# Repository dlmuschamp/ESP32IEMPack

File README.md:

# ESP32 Wireless IEM Pack

A first-pass wireless in-ear monitor (IEM) system: one ESP32 transmitter pack and one ESP32 receiver pack. The RX path is `ESP-NOW → ESP32 → I2S → PCM5102 DAC → volume pot → MAX97220A headphone amp → 3.5 mm jack`.

This repo is a work in progress. The breadboard version plays audio. The KiCad project in `KiCad/RX_SKETCHES/` is that breadboard transferred onto hierarchical sheets — not a finished layout. There is **no display on this version**.

## What this version is (and is not)

| | This version | Not this version |
|---|---|---|
| Display | None | The old 1.54" TFT / Arduino UI idea |
| RX power | USB-C from a 10,000 mAh 5 V power bank → LM3940 3.3 V | TP4056 + 2000 mAh LiPo / 3xAA |
| TX power | The same kind of 10,000 mAh 5 V power bank as the RX | A different battery chemistry or a shared bank |
| Radio | ESP32-WROOM-32U + **`ANT1` 2.4 GHz U.FL pigtail** on `esp_rx` | On-module PCB antenna (that is the 32E / 32D) |
| Audio | I2S to a PCM5102, then a headphone amp | I2C (the DAC is I2S) |
| PCB | Footprint dump / ratsnest only | Routed board ready to order |

TX and RX each get their **own** identical 10,000 mAh bank. Do not power both packs from one bank if you want them to roam independently.

## Repo map

```
main/                  ESP-IDF C firmware
  rig_shared.h         Shared packet / state types (TX and RX)
  tx.c                 Transmitter (ESP-NOW + ADC pot + LED). Audio fill is still TODO.
  rx.c                 Receiver stub. Set IEM_NODE=RX when it has an app_main.
  square_wave_test.c   Bench I2S tone used to prove the DAC path
  sniffer.c            Monitor / debug helper
KiCad/RX_SKETCHES/     RX hierarchical schematic (WIP)
KiCad/TX_SKETCHES/     TX placeholder
KiCad/Custom_Part_Downloads/  SnapEDA symbols / footprints used by the RX project
```

Build a node with ESP-IDF after exporting the target:

```bash
IEM_NODE=TX idf.py build
# IEM_NODE=RX or IEM_NODE=MON once those mains are complete
```

`main/CMakeLists.txt` refuses to build if `IEM_NODE` is missing. That is intentional so you do not flash the wrong image.

## Hardware (RX 1.0.0 KiCad)

Hierarchical sheets, in signal order:

1. **`pwr_mgmt`** — USB-C (CC pulldowns), CP2102C UART bridge, LM3940 5 V → 3.3 V
2. **`esp_rx`** — ESP32-WROOM-32U + `ANT1` (U.FL pigtail / 2.4 GHz antenna)
3. **`dac`** — PCM5102
4. **`vol_ctrl`** — dual-gang log pot + 0% switch
5. **`amp`** — MAX97220A to the 3.5 mm jack

### Firmware I2S map (do not "improve" these GPIOs)

These match the working breadboard and `main/square_wave_test.c`:

| Hierarchical label | ESP32 GPIO | Firmware name |
|---|---|---|
| `BCK` | IO33 | `BCK_PIN` |
| `LRCLK` | IO32 | `LRCK_PIN` |
| `DIN` | IO25 | `DOUT_PIN` (ESP data **out** to the DAC data **in**) |

UART programming: `TXD` = TXD0/IO1, `RXD` = RXD0/IO3. Auto-program straps: `ESP_EN` = EN, `ESP_IO0` = IO0.

### Antenna (`ANT1` on `esp_rx`)

The **32U** module has a U.FL connector and **no PCB antenna**. `ANT1` is a BOM / documentation part: a **2.4 GHz, 50 Ω antenna on a U.FL / IPEX pigtail** that mates to the connector already on the module. It is not wired to a GPIO. It has no PCB footprint — you buy the pigtail, you do not etch an antenna.

If you would rather have an on-board antenna later, that is a different module (WROOM-32E / 32D), not a missing copper pour on the 32U.

### Analog (PCM5102 datasheet vs experiments)

The PCM5102 datasheet analog network for a ~10 kΩ load is already on the DAC sheet (`R16`/`R17` 470 Ω, `C20`/`C21` 2.2 nF):

`OUTL/OUTR → 470 Ω series → PRE_POT`, with **2.2 nF from that node to GND**.

The MAX97220A input impedance is also about **10 kΩ**, so that filter is the right starting point. The experimental 1 kΩ / 10 Ω pad on `vol_ctrl` is **DNP**, with a short across the 1 kΩ positions so an empty series part does not open the audio path.

MAX97220A voltage gain is **fixed +3.5 dB**. Input network resistors `R1–R6`, `R9`, `R10` are **DNP** on hand-built protos so you can try values. Populate them (start 10 kΩ) only if you order a fully assembled board. Use a MAX97220**D** if you want resistor-programmed gain.

### Hand assembly

Schematic footprint fields are **0805**. Use 0805 for every resistor and capacitor you will solder yourself, including 10 / 22 / 33 µF. 0603 is OK if you are already comfortable. Do not use 0402 or 0201. The `.kicad_pcb` still shows 0201 until you **Update PCB from Schematic**.

ICs stay their real packages (WROOM module, TSSOP-20, TQFN-16, SOT-223, WQFN-24).

## Current status

- [x] Breadboard RX path plays (ESP32 I2S → PCM5102 → amp → IEMs)
- [x] Repo + KiCad folder split (`RX_SKETCHES` / `TX_SKETCHES`)
- [x] RX hierarchical schematic transferred from the breadboard (WIP)
- [x] Hierarchical labels rewired; `ANT1` added on `esp_rx`
- [ ] Buy / fit the U.FL pigtail; confirm ESP-NOW range
- [ ] Finish `tx.c` audio packet fill / `rx.c` I2S consume
- [ ] Run ERC, then floorplan and route the RX PCB
- [ ] TX schematic (same 10,000 mAh USB-C bank idea)

No TFT / SPI display work on this revision.

## Common KiCad / first-board mistakes

This is a first KiCad project *and* a first C / ESP-IDF / multi-IC audio board. The list below is the stuff that already bit this schematic. Check it every time you move a part or add a hierarchical label.

### 1. Rotating a symbol does not remap pin numbers

Pin 3 is still `EN` after a 270° rotate. KiCad only rotates the **drawing** and the **sheet coordinates** of the pins around the symbol origin. Hierarchical labels and wires that stay put will attach to whichever pin rotated into that spot.

After any rotate: click each pin, read the name, then move the label onto **that** pin. Do not assume “left side is still EN.”

### 2. Hierarchical labels connect through wires, not vibes

A label sitting near a pin is not connected. ERC and the ratsnest follow **wires and pin ends**. After a rotate, a label can look “on” the chip and still sit on empty space or on the wrong pin (`ESP_IO0` on `EN`, `BCK` on `DEMP`, `SHDN_SIGNAL` on `C1N`).

Triple-check every hierarchical label against the **pin name**, not the side of the box.

### 3. Same-ish names are different pins

| You meant | Easy to hit instead | What happens |
|---|---|---|
| PCM5102 `BCK` / `DIN` / `LRCK` | `DEMP` / `XSMT` / `FMT` | DAC never gets PCM; clocks toggle config bits |
| MAX97220 `~{SHDN}` | `C1N` (charge-pump cap) | Volume switch does not mute; VSS pump breaks |
| ESP `TXD0` / `RXD0` | `SENSOR_VN` / empty space | USB-C UART programming dies |
| I2S | I2C | Wrong bus, wrong pins, wrong mental model |

Read the pin **name** in the status bar before you drop the label.

### 4. Firmware GPIO numbers are the contract

`#define BCK_PIN 33` is IO33 on the module, period. Do not “clean up” the schematic onto IO18/19/23 unless you change the C defines too. Label `DIN` on the DAC is the ESP’s **DOUT**.

### 5. The footprint field is a part you have to buy and solder

If the field says `R_0201_0603Metric`, you will get 0201s. Bulk 10 µF parts basically do not exist in 0201, and you will not hand-assemble them. Set 0805 (or 0603) **before** you Update PCB from Schematic.

### 6. DNP does not delete the net

KiCad “Do not populate” still leaves the schematic wires. If you DNP a **series** resistor, the path goes open unless you add a solder-bridge / short. If you DNP a **shunt**, leaving the pads empty is correct (no short to GND).

### 7. 32U vs 32E, A vs D, datasheet vs doodle

- **32U** = U.FL only. **32E/32D** = PCB antenna. Pick one and BOM the matching RF parts.
- **MAX97220A** ≠ **MAX97220D**. The letter is the gain mode.
- Prefer the datasheet application circuit (470 Ω + 2.2 nF here) over a pad you tried on the bench, unless you measured why the pad is better.

### 8. The `.kicad_pcb` is not a board until it has Edge.Cuts and tracks

A pile of footprints with a ratsnest is a placeholder. After schematic net or footprint changes, **Update PCB from Schematic**. Do not send that file to a fab.

### 9. Power and analog will buzz on a breadboard

Long jumpers, no ground plane, and an ESP32 radio next to a DAC is a buzz/hiss machine. That does not automatically mean the circuit is wrong. A PCB with short I2S, local decoupling, and a solid GND will almost certainly be quieter. It is not guaranteed to be silent on the first spin.

### 10. Keep the README honest

If the schematic is USB-C + LDO and no display, the README must not still say TP4056 + LiPo + TFT. Future-you (and anyone reviewing a PR) will trust the wrong power tree.

## Author

Damian Luciano Muschamp

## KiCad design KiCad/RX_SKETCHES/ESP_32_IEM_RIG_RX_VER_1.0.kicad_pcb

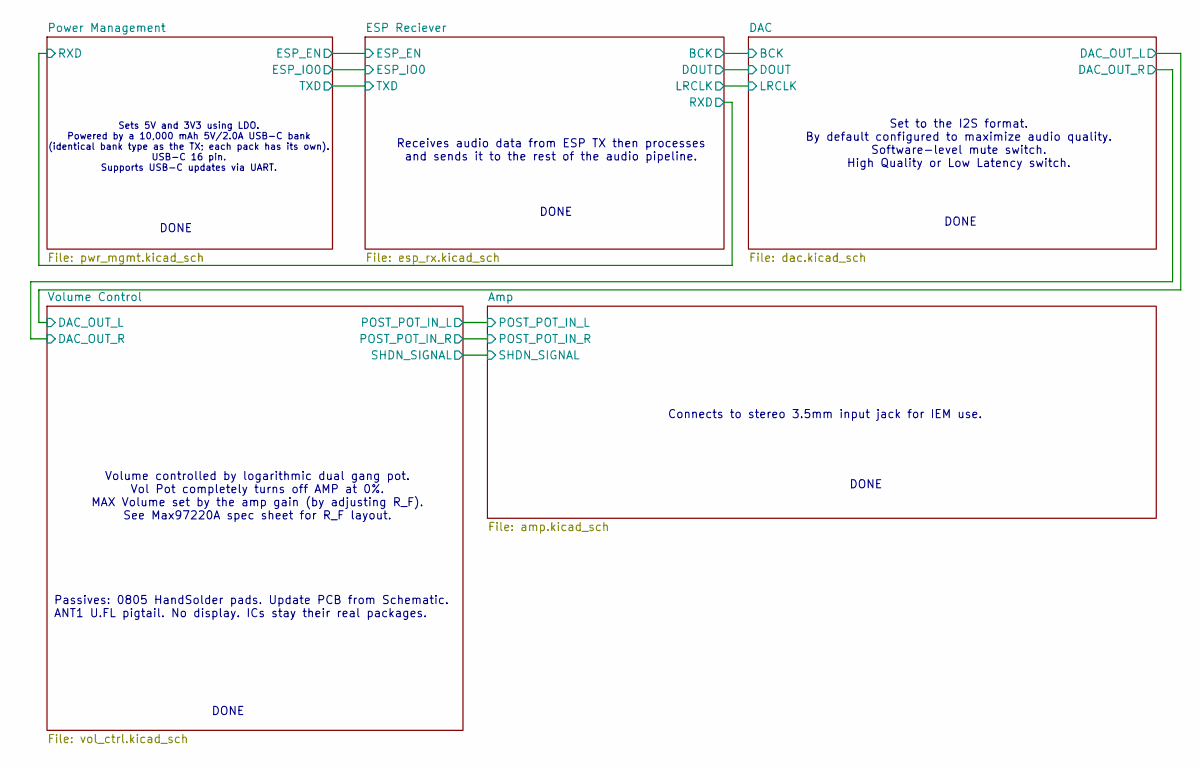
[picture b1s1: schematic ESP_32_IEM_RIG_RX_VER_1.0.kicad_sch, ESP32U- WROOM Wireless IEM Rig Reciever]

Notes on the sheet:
DONE
Volume controlled by logarithmic dual gang pot. Vol Pot completely turns off AMP at 0%. MAX Volume set by the amp gain (by adjusting R_F). See Max97220A spec sheet for R_F layout.
Receives audio data from ESP TX then processes and sends it to the rest of the audio pipeline.
Connects to stereo 3.5mm input jack for IEM use.
Passives: 0805 HandSolder pads. Update PCB from Schematic. ANT1 U.FL pigtail. No display. ICs stay their real packages.
Sets 5V and 3V3 using LDO. Powered by a 10,000 mAh 5V/2.0A USB-C bank (identical bank type as the TX; each pack has its own). USB-C 16 pin. Supports USB-C updates via UART.
Set to the I2S format. By default configured to maximize audio quality. Software-level mute switch. High Quality or Low Latency switch.

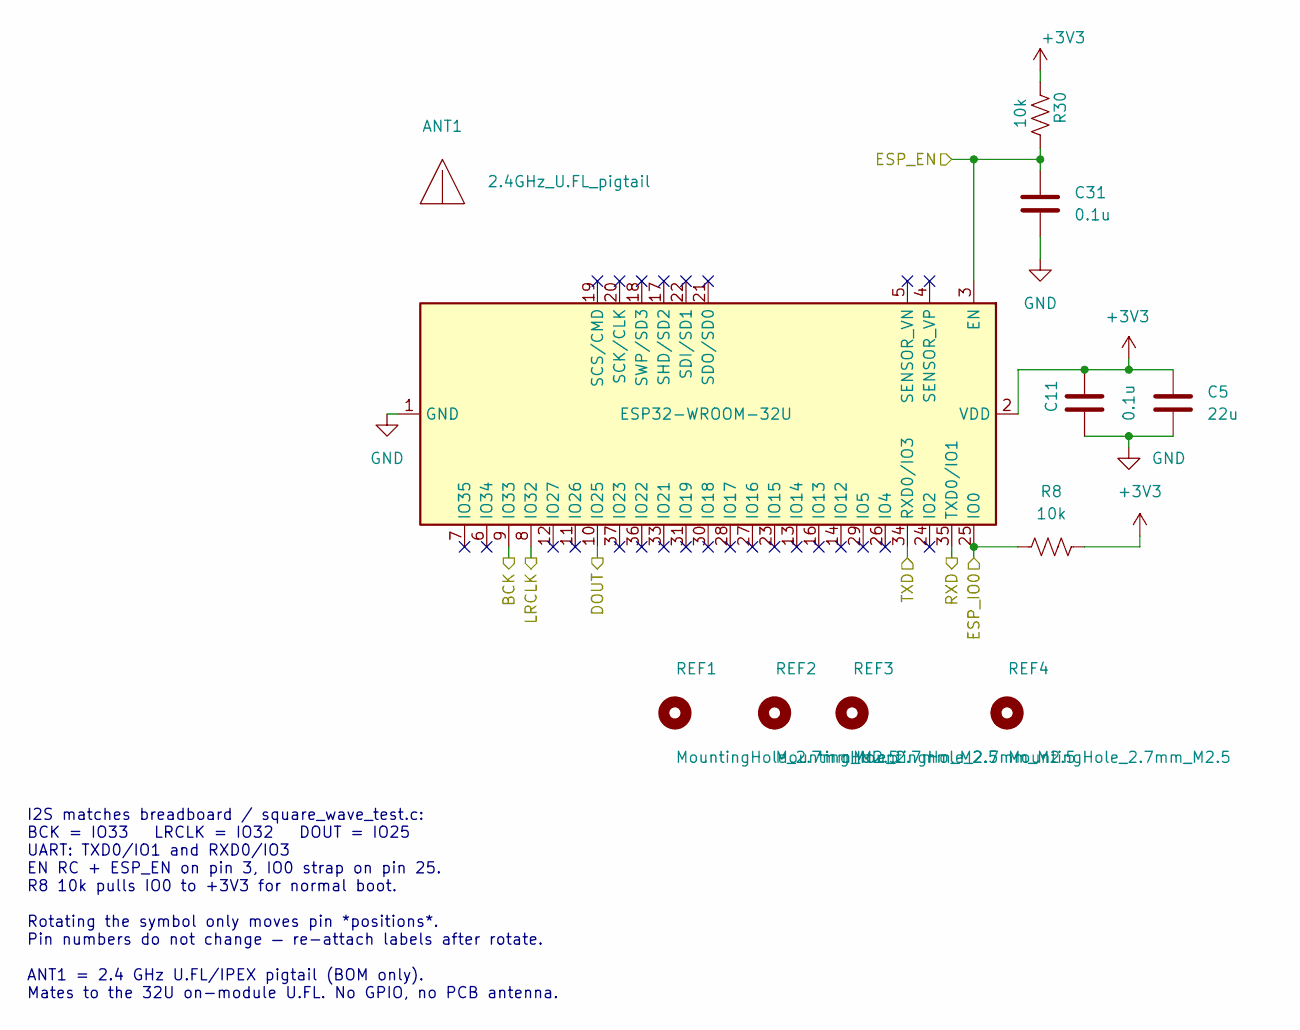
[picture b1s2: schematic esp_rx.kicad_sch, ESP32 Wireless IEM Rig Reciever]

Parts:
ANT1: 2.4GHz_U.FL_pigtail
C5: 22u; C_0805_2012Metric_Pad1.18x1.45mm_HandSolder
C11, C31: 0.1u; C_0805_2012Metric_Pad1.18x1.45mm_HandSolder
R8, R30: 10k; R_0805_2012Metric_Pad1.20x1.40mm_HandSolder
REF1, REF2, REF3, REF4: MountingHole_2.7mm_M2.5
U2: ESP32-WROOM-32U

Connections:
+3V3: C5.1, C11.1, R8.1, R30.2, U2.2 (VDD); also elsewhere on the board
/DAC/BCK: U2.9 (IO33); also elsewhere on the board
/DAC/DOUT: U2.10 (IO25); also elsewhere on the board
/DAC/LRCLK: U2.8 (IO32); also elsewhere on the board
/ESP Reciever/ESP_EN: C31.1, R30.1, U2.3 (EN); also elsewhere on the board
/ESP Reciever/ESP_IO0: R8.2, U2.25 (IO0); also elsewhere on the board
/ESP Reciever/RXD: U2.35 (TXD0/IO1); also elsewhere on the board
/ESP Reciever/TXD: U2.34 (RXD0/IO3); also elsewhere on the board
GND: C5.2, C11.2, C31.2, U2.1 (GND), U2.15 (GND), U2.38 (GND), U2.39 (GND); also elsewhere on the board

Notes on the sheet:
I2S matches breadboard / square_wave_test.c: BCK = IO33 LRCLK = IO32 DOUT = IO25 UART: TXD0/IO1 and RXD0/IO3 EN RC + ESP_EN on pin 3, IO0 strap on pin 25. R8 10k pulls IO0 to +3V3 for normal boot. Rotating the symbol only moves pin *positions*. Pin numbers do not change — re-attach labels after rot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

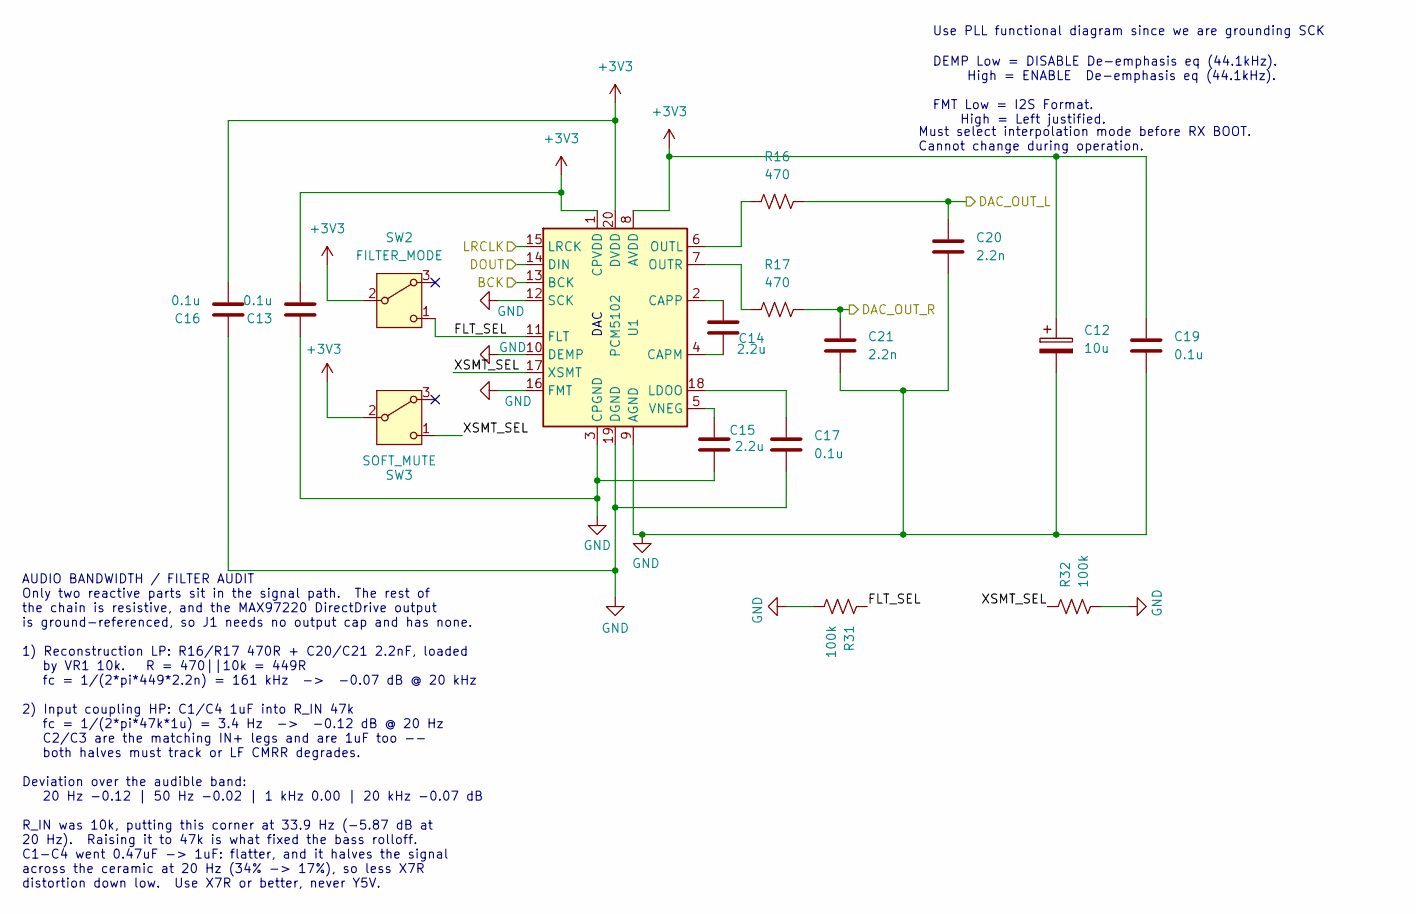
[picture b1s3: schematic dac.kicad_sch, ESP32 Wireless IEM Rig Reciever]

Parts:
C12: 10u; C_0805_2012Metric_Pad1.18x1.45mm_HandSolder
C13, C16, C17, C19: 0.1u; C_0805_2012Metric_Pad1.18x1.45mm_HandSolder
C14, C15: 2.2u; C_0805_2012Metric_Pad1.18x1.45mm_HandSolder
C20, C21: 2.2n; C_0805_2012Metric_Pad1.18x1.45mm_HandSolder
R16, R17: 470; R_0805_2012Metric_Pad1.20x1.40mm_HandSolder
R31, R32: 100k; R_0805_2012Metric_Pad1.20x1.40mm_HandSolder
SW2: FILTER_MODE; SW_SPDT_Shouhan_MSK12C02
SW3: SOFT_MUTE; SW_SPDT_Shouhan_MSK12C02
U1: PCM5102; TSSOP-20_4.4x6.5mm_P0.65mm

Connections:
+3V3: C12.1, C13.2, C16.2, C19.1, SW2.2 (B), SW3.2 (B), U1.1 (CPVDD), U1.8 (AVDD), U1.20 (DVDD); also elsewhere on the board
/DAC/BCK: U1.13 (BCK); also elsewhere on the board
/DAC/DAC_OUT_L: C20.1, R16.2; also elsewhere on the board
/DAC/DAC_OUT_R: C21.1, R17.2; also elsewhere on the board
/DAC/DOUT: U1.14 (DIN); also elsewhere on the board
/DAC/FLT_SEL: R31.1, SW2.1 (C), U1.11 (FLT)
/DAC/LRCLK: U1.15 (LRCK); also elsewhere on the board
/DAC/XSMT_SEL: R32.1, SW3.1 (C), U1.17 (XSMT)
GND: C12.2, C13.1, C15.2, C16.1, C17.2, C19.2, C20.2, C21.2, R31.2, R32.2, U1.3 (CPGND), U1.9 (AGND), U1.10 (DEMP), U1.12 (SCK), U1.16 (FMT), U1.19 (DGND); also elsewhere on the board
unnamed: C14.2, U1.4 (CAPM)
unnamed: C14.1, U1.2 (CAPP)
unnamed: C17.1, U1.18 (LDOO)
unnamed: R16.1, U1.6 (OUTL)
unnamed: R17.1, U1.7 (OUTR)
unnamed: C15.1, U1.5 (VNEG)

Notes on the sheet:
AUDIO BANDWIDTH / FILTER AUDIT Only two reactive parts sit in the signal path. The rest of the chain is resistive, and the MAX97220 DirectDrive output is ground-referenced, so J1 needs no output cap and has none. 1) Reconstruction LP: R16/R17 470R + C20/C21 2.2nF, loaded by VR1 10k. R = 470||10k = 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
DAC
DEMP Low = DISABLE De-emphasis eq (44.1kHz). High = ENABLE De-emphasis eq (44.1kHz). FMT Low = I2S Format. High = Left justified.
Use PLL functional diagram since we are grounding SCK
Must select interpolation mode before RX BOOT. Cannot change during operation.

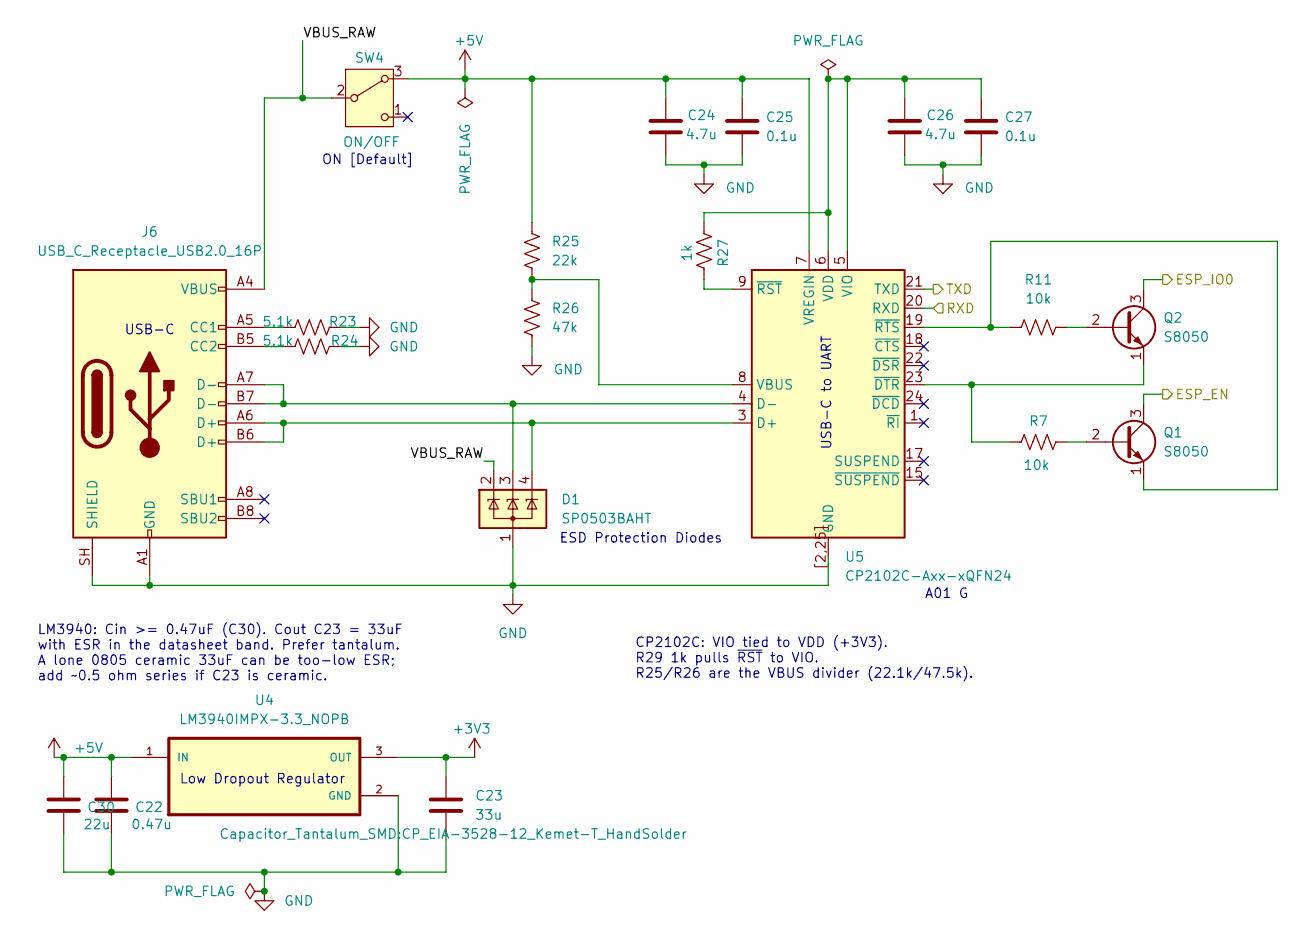
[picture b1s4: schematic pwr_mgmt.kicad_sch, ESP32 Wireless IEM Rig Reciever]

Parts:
C22: 0.47u; C_0805_2012Metric_Pad1.18x1.45mm_HandSolder
C23: 33u; CP_EIA-3528-12_Kemet-T_HandSolder
C24, C26: 4.7u; C_0805_2012Metric_Pad1.18x1.45mm_HandSolder
C25, C27: 0.1u; C_0805_2012Metric_Pad1.18x1.45mm_HandSolder
C30: 22u; C_0805_2012Metric_Pad1.18x1.45mm_HandSolder
D1: SP0503BAHT; SOT-143
J6: USB_C_Receptacle_USB2.0_16P; USB_C_Receptacle_GCT_USB4105-xx-A_16P_TopMnt_Horizontal
Q1, Q2: S8050; SOT-23
R7, R11: 10k; R_0805_2012Metric_Pad1.20x1.40mm_HandSolder
R23, R24: 5.1k; R_0805_2012Metric_Pad1.20x1.40mm_HandSolder
R25: 22k; R_0805_2012Metric_Pad1.20x1.40mm_HandSolder
R26: 47k; R_0805_2012Metric_Pad1.20x1.40mm_HandSolder
R27: 1k; R_0805_2012Metric_Pad1.20x1.40mm_HandSolder
SW4: ON/OFF; SW_SPDT_Shouhan_MSK12C02
U4: LM3940IMPX-3.3_NOPB; SOT230P700X180-4N
U5: CP2102C-Axx-xQFN24; WQFN-24-1EP_4x4mm_P0.5mm_EP2.45x2.45mm

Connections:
+3V3: C23.1, U4.3 (OUT); also elsewhere on the board
+5V: C22.1, C24.1, C25.1, C30.1, R25.1, SW4.3 (A), U4.1 (IN), U5.7 (VREGIN)
/ESP Reciever/ESP_EN: Q1.3 (C); also elsewhere on the board
/ESP Reciever/ESP_IO0: Q2.3 (C); also elsewhere on the board
/ESP Reciever/RXD: U5.20 (RXD); also elsewhere on the board
/ESP Reciever/TXD: U5.21 (TXD); also elsewhere on the board
/Power Management/VBUS_RAW: D1.2 (K), J6.A4 (VBUS), J6.A9 (VBUS), J6.B4 (VBUS), J6.B9 (VBUS), SW4.2 (B)
GND: C22.2, C23.2, C24.2, C25.2, C26.2, C27.2, C30.2, D1.1 (A), J6.A1 (GND), J6.A12 (GND), J6.B1 (GND), J6.B12 (GND), J6.SH (SHIELD), R23.2, R24.2, R26.2, U4.2 (GND), U4.4 (GND), U5.2 (GND), U5.25 (GND), U5.[2,25] (GND); also elsewhere on the board
unnamed: J6.A5 (CC1), R23.1
unnamed: J6.B5 (CC2), R24.1
unnamed: Q1.2 (B), R7.2
unnamed: Q1.1 (E), R11.1, U5.19 (~RTS)
unnamed: Q2.2 (B), R11.2
unnamed: Q2.1 (E), R7.1, U5.23 (~DTR)
unnamed: D1.4 (K), J6.A6 (D+), J6.B6 (D+), U5.3 (D+)
unnamed: D1.3 (K), J6.A7 (D-), J6.B7 (D-), U5.4 (D-)
unnamed: R25.2, R26.1, U5.8 (VBUS)
unnamed: C26.1, C27.1, R27.2, U5.5 (VIO), U5.6 (VDD)
unnamed: R27.1, U5.9 (~RST)

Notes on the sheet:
A01 G
USB-C
LM3940: Cin >= 0.47uF (C30). Cout C23 = 33uF with ESR in the datasheet band. Prefer tantalum. A lone 0805 ceramic 33uF can be too-low ESR; add ~0.5 ohm series if C23 is ceramic.
Low Dropout Regulator
ON [Default]
ESD Protection Diodes
USB-C to UART
CP2102C: VIO tied to VDD (+3V3). R29 1k pulls ~{RST} to VIO. R25/R26 are the VBUS divider (22.1k/47.5k).

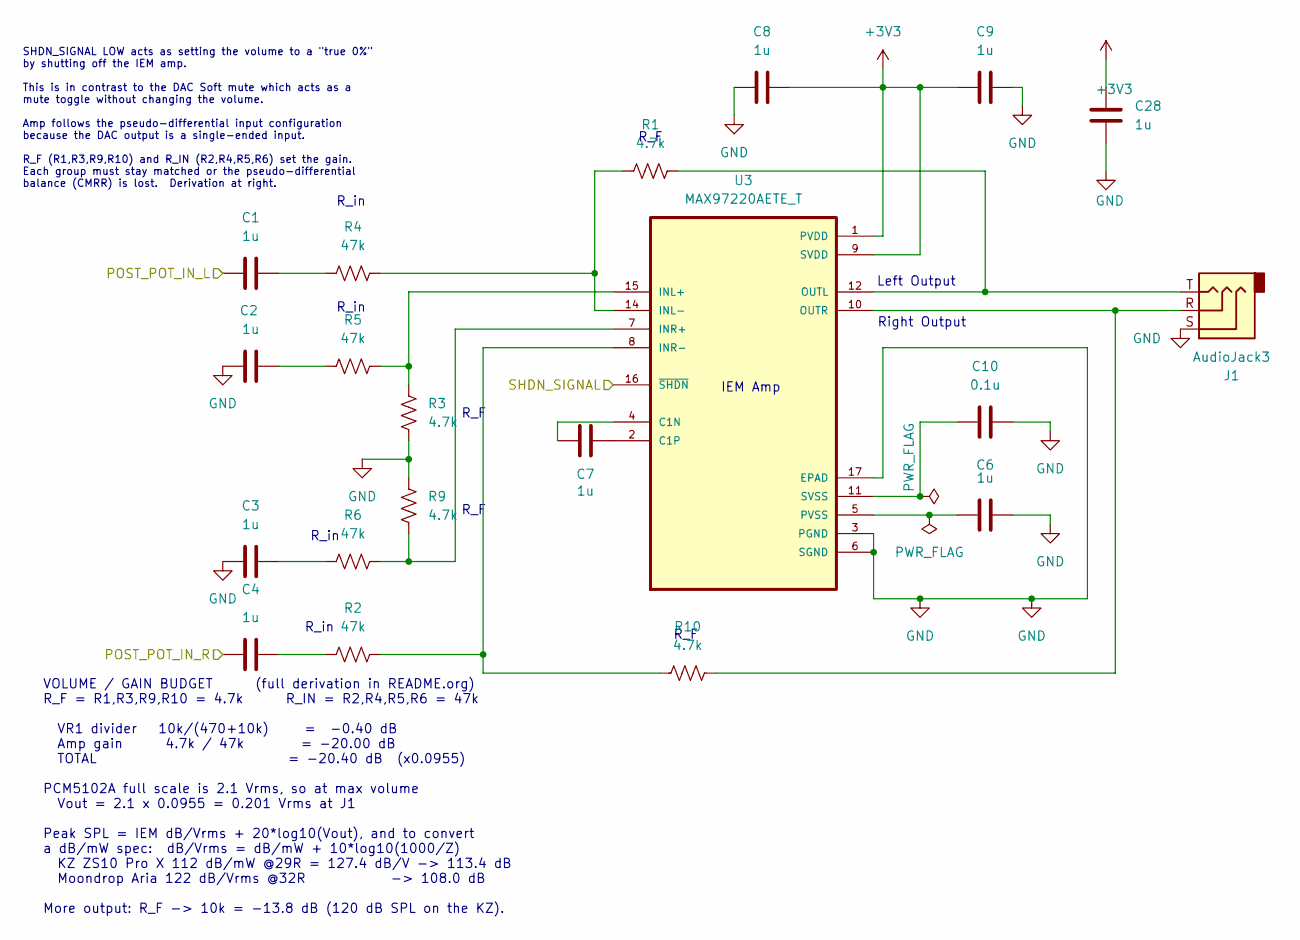
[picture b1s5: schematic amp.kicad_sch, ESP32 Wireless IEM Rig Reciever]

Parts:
C1, C2, C3, C4, C6, C7, C8, C9, C28: 1u; C_0805_2012Metric_Pad1.18x1.45mm_HandSolder
C10: 0.1u; C_0805_2012Metric_Pad1.18x1.45mm_HandSolder
J1: AudioJack3; Jack_3.5mm_CUI_SJ-3523-SMT_Horizontal
R1, R3, R9, R10: 4.7k; R_0805_2012Metric_Pad1.20x1.40mm_HandSolder
R2, R4, R5, R6: 47k; R_0805_2012Metric_Pad1.20x1.40mm_HandSolder
U3: MAX97220AETE_T; QFN50P300X300X80-17N

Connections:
+3V3: C8.2, C9.1, C28.1, U3.1 (PVDD), U3.9 (SVDD), U3.13 (SVDD); also elsewhere on the board
/Amp/POST_POT_IN_L: C1.1; also elsewhere on the board
/Amp/POST_POT_IN_R: C4.1; also elsewhere on the board
/Amp/SHDN_SIGNAL: U3.16 (~SHDN); also elsewhere on the board
GND: C2.1, C3.1, C6.2, C8.1, C9.2, C10.2, C28.2, J1.S, R3.2, R9.1, U3.3 (PGND), U3.6 (SGND), U3.17 (EPAD); also elsewhere on the board
unnamed: C1.2, R4.1
unnamed: C2.2, R5.1
unnamed: C3.2, R6.1
unnamed: C4.2, R2.1
unnamed: C7.2, U3.4 (C1N)
unnamed: C7.1, U3.2 (C1P)
unnamed: R3.1, R5.2, U3.15 (INL+)
unnamed: R1.1, R4.2, U3.14 (INL-)
unnamed: R6.2, R9.2, U3.7 (INR+)
unnamed: R2.2, R10.1, U3.8 (INR-)
unnamed: J1.T, R1.2, U3.12 (OUTL)
unnamed: J1.R, R10.2, U3.10 (OUTR)
unnamed: C6.1, U3.5 (PVSS)
unnamed: C10.1, U3.11 (SVSS)

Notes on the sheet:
Right Output
IEM Amp
R_in
R_F
VOLUME / GAIN BUDGET (full derivation in README.org) R_F = R1,R3,R9,R10 = 4.7k R_IN = R2,R4,R5,R6 = 47k VR1 divider 10k/(470+10k) = -0.40 dB Amp gain 4.7k / 47k = -20.00 dB TOTAL = -20.40 dB (x0.0955) PCM5102A full scale is 2.1 Vrms, so at max volume Vout = 2.1 x 0.0955 = 0.201 Vrms at J1 Peak SPL 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
Left Output
SHDN_SIGNAL LOW acts as setting the volume to a "true 0%" by shutting off the IEM amp. This is in contrast to the DAC Soft mute which acts as a mute toggle without changing the volume. Amp follows the pseudo-differential input configuration because the DAC output is a single-ended input. R_F (R1,R3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

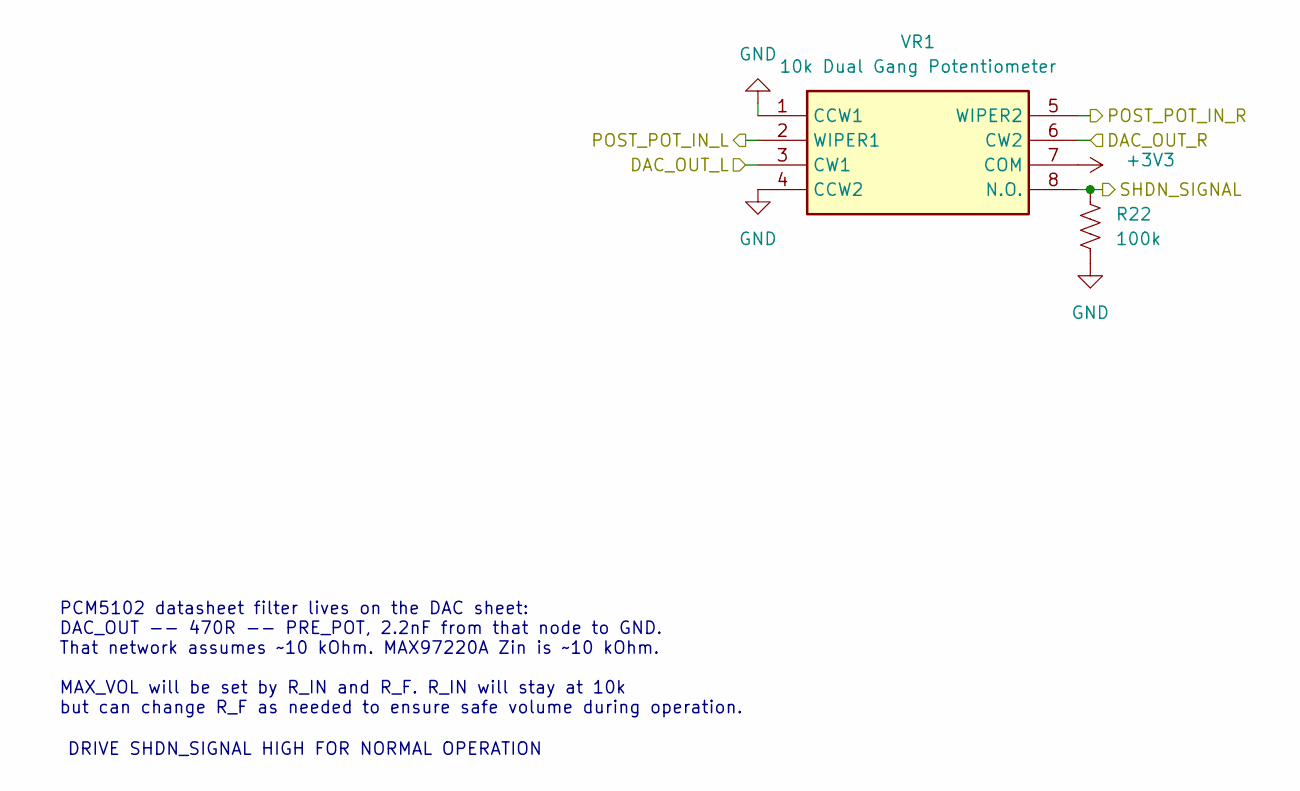
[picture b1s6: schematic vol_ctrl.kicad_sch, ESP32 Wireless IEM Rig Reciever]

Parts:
R22: 100k; R_0805_2012Metric_Pad1.20x1.40mm_HandSolder
VR1: 10k Dual Gang Potentiometer; PTN09S2H10120K1A; Manufacturer_Part_Number PTN09S2-H10120K1A

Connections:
+3V3: VR1.7 (COM); also elsewhere on the board
/Amp/POST_POT_IN_L: VR1.2 (WIPER1); also elsewhere on the board
/Amp/POST_POT_IN_R: VR1.5 (WIPER2); also elsewhere on the board
/Amp/SHDN_SIGNAL: R22.1, VR1.8 (N.O.); also elsewhere on the board
/DAC/DAC_OUT_L: VR1.3 (CW1); also elsewhere on the board
/DAC/DAC_OUT_R: VR1.6 (CW2); also elsewhere on the board
GND: R22.2, VR1.1 (CCW1), VR1.4 (CCW2); also elsewhere on the board

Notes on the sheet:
PCM5102 datasheet filter lives on the DAC sheet: DAC_OUT -- 470R -- PRE_POT, 2.2nF from that node to GND. That network assumes ~10 kOhm. MAX97220A Zin is ~10 kOhm. MAX_VOL will be set by R_IN and R_F. R_IN will stay at 10k but can change R_F as needed to ensure safe volume during operation.
DRIVE SHDN_SIGNAL HIGH FOR NORMAL OPERATION

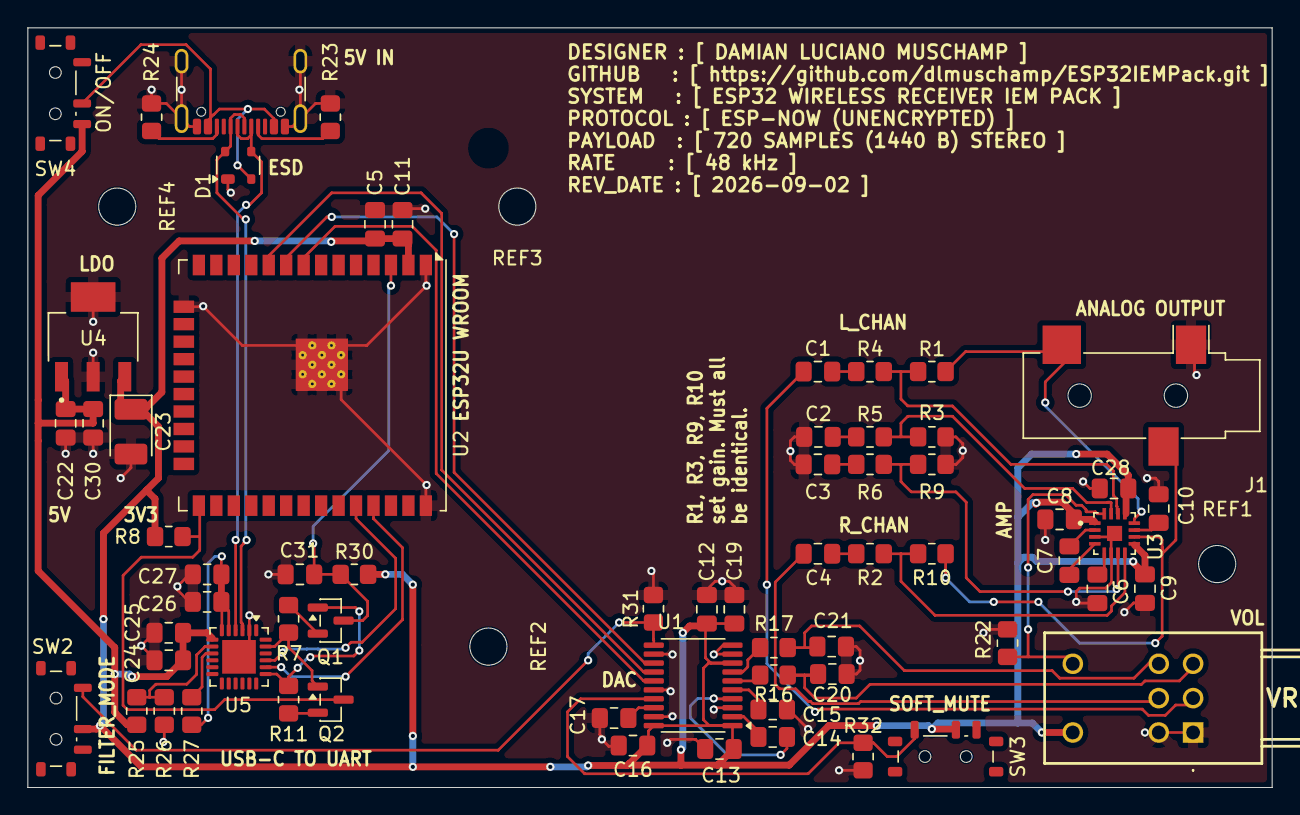
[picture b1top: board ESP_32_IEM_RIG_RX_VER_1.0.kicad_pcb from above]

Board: 2 copper layers, 90.5 x 55.2 mm, 69 parts (0 on the bottom side), 49 nets.

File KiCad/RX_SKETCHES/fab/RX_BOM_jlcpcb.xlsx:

Comment | Designator | Footprint | Qty | LCSC Part #
1u | C1,C2,C3,C4,C6,C7,C8,C9,C28 | Capacitor_SMD:C_0805_2012Metric_Pad1.18x1.45mm_HandSolder | 9
22u | C5,C30 | Capacitor_SMD:C_0805_2012Metric_Pad1.18x1.45mm_HandSolder | 2
0.1u | C10,C11,C13,C16,C17,C19,C25,C27,C31 | Capacitor_SMD:C_0805_2012Metric_Pad1.18x1.45mm_HandSolder | 9
10u | C12 | Capacitor_SMD:C_0805_2012Metric_Pad1.18x1.45mm_HandSolder | 1
2.2u | C14,C15 | Capacitor_SMD:C_0805_2012Metric_Pad1.18x1.45mm_HandSolder | 2
2.2n | C20,C21 | Capacitor_SMD:C_0805_2012Metric_Pad1.18x1.45mm_HandSolder | 2
0.47u | C22 | Capacitor_SMD:C_0805_2012Metric_Pad1.18x1.45mm_HandSolder | 1
33u | C23 | Capacitor_SMD:C_0805_2012Metric_Pad1.18x1.45mm_HandSolder | 1
4.7u | C24,C26 | Capacitor_SMD:C_0805_2012Metric_Pad1.18x1.45mm_HandSolder | 2
SP0503BAHT | D1 | Package_TO_SOT_SMD:SOT-143 | 1
AudioJack3 | J1 | Connector_Audio:Jack_3.5mm_CUI_SJ-3523-SMT_Horizontal | 1
USB_C_Receptacle_USB2.0_16P | J6 | Connector_USB:USB_C_Receptacle_GCT_USB4105-xx-A_16P_TopMnt_Horizontal | 1
S8050 | Q1,Q2 | Package_TO_SOT_SMD:SOT-23 | 2
4.7k | R1,R3,R9,R10 | Resistor_SMD:R_0805_2012Metric_Pad1.20x1.40mm_HandSolder | 4
47k | R2,R4,R5,R6 | Resistor_SMD:R_0805_2012Metric_Pad1.20x1.40mm_HandSolder | 4
10k | R7,R8,R11,R30 | Resistor_SMD:R_0805_2012Metric_Pad1.20x1.40mm_HandSolder | 4
470 | R16,R17 | Resistor_SMD:R_0805_2012Metric_Pad1.20x1.40mm_HandSolder | 2
100k | R22,R31,R32 | Resistor_SMD:R_0805_2012Metric_Pad1.20x1.40mm_HandSolder | 3
5.1k | R23,R24 | Resistor_SMD:R_0805_2012Metric_Pad1.20x1.40mm_HandSolder | 2
22.1k | R25 | Resistor_SMD:R_0805_2012Metric_Pad1.20x1.40mm_HandSolder | 1
47.5k | R26 | Resistor_SMD:R_0805_2012Metric_Pad1.20x1.40mm_HandSolder | 1
1k | R27 | Resistor_SMD:R_0805_2012Metric_Pad1.20x1.40mm_HandSolder | 1
PCM5102 | U1 | Package_SO:TSSOP-20_4.4x6.5mm_P0.65mm | 1
ESP32-WROOM-32U | U2 | RF_Module:ESP32-WROOM-32U | 1
MAX97220AETE_T | U3 | MAX97220AETE_T:QFN50P300X300X80-17N | 1
LM3940IMPX-3.3_NOPB | U4 | LM3940IMPX-3.3_NOPB:SOT230P700X180-4N | 1
CP2102C-Axx-xQFN24 | U5 | Package_DFN_QFN:WQFN-24-1EP_4x4mm_P0.5mm_EP2.45x2.45mm | 1
MSK-12C02 SPDT slide switch | SW2,SW3,SW4 | Button_Switch_SMD:SW_SPDT_Shouhan_MSK12C02 | 3
